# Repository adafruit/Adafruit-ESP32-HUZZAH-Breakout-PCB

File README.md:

## Adafruit HUZZAH32 PCB

<a href="http://www.adafruit.com/products/4172"><br/>
Click here to purchase one from the Adafruit shop</a>

PCB files for the Adafruit HUZZAH32. 

Format is EagleCAD schematic and board layout
* https://www.adafruit.com/product/4172

### Description

Squeeeeze down your next ESP32 project to its bare-bones essential with the **Adafruit HUZZAH32 Breakout**. This breakout is basically the 'big sister' of our HUZZAH 8266, but instead of an ESP8266 it has the '32! We've pared down our popular [Feather ESP32](https://www.adafruit.com/product/3405), removing the battery charger and USB-serial converter. You just get a regulator, some protection diodes, two buttons and an LED. For some projects, where price and size are at a premium, you can program this board over the 'FTDI cable' breakout when needed, and leave it alone otherwise.

Note that this board doesn't come with a USB to serial converter chip and auto-reset circuit. Instead, you will need to plug in a [CP2104 Friend](https://www.adafruit.com/product/3309) or [FTDI cable](https://www.adafruit.com/product/70). Then, before uploading code, put it into bootloader mode by holding down the GPIO #0 button and clicking Reset button, then releasing the #0 button.

That module in the middle of the breakout contains a dual-core ESP32 chip, 4 MB of SPI Flash, tuned antenna, and all the passives you need to take advantage of this powerful new processor. The ESP32 has both WiFi and Bluetooth Classic/LE support. That means it's perfect for just about any wireless or Internet-connected project.

The ESP32 is a perfect upgrade from the ESP8266 that has been so popular. In comparison, the ESP32 has way more GPIO, plenty of analog inputs, two analog outputs, multiple extra peripherals (like a spare UART), two cores so you don't have to yield to the WiFi manager, much higher-speed processor, etc. etc!

Comes fully assembled and tested, pre-programmed with ESP32 SPI WiFi co-processor firmware that [you can use in CircuitPython to use this into a WiFi co-processsor over SPI + 2 pins.](https://github.com/ladyada/Adafruit_CircuitPython_ESP32SPI) We also toss in some header so you can solder it in and plug into a solderless breadboard. 

Here are [specifications from Espressif about the ESP32](https://espressif.com/en/products/hardware/esp32/overview):

 * 240 MHz dual core Tensilica LX6 microcontroller with 600 DMIPS
 * Integrated 520 KB SRAM
 * Integrated 802.11b/g/n HT40 Wi-Fi transceiver, baseband, stack and LWIP
 * Integrated dual mode Bluetooth (classic and BLE)
 * 4 MByte flash include in the WROOM32 module
 * On-board PCB antenna
 * Ultra-low noise analog amplifier
 * Hall sensor
 * 10x capacitive touch interface
 * 32 kHz crystal oscillator
 * 3 x UARTs (only two are configured by default in the Feather Arduino IDE support, one UART is used for bootloading/debug)
 * 3 x SPI (only one is configured by default in the Feather Arduino IDE support)
 * 2 x I2C (only one is configured by default in the Feather Arduino IDE support)
 * 12 x ADC input channels
 * 2 x I2S Audio
 * 2 x DAC
 * PWM/timer input/output available on every GPIO pin
 * OpenOCD debug interface with 32 kB TRAX buffer
 * SDIO master/slave 50 MHz
 * SD-card interface support

### License

Adafruit invests time and resources providing this open source design, please support Adafruit and open-source hardware by purchasing products from [Adafruit](https://www.adafruit.com)!

Designed by Limor Fried/Ladyada for Adafruit Industries.

Creative Commons Attribution/Share-Alike, all text above must be included in any redistribution. 
See license.txt for additional details.

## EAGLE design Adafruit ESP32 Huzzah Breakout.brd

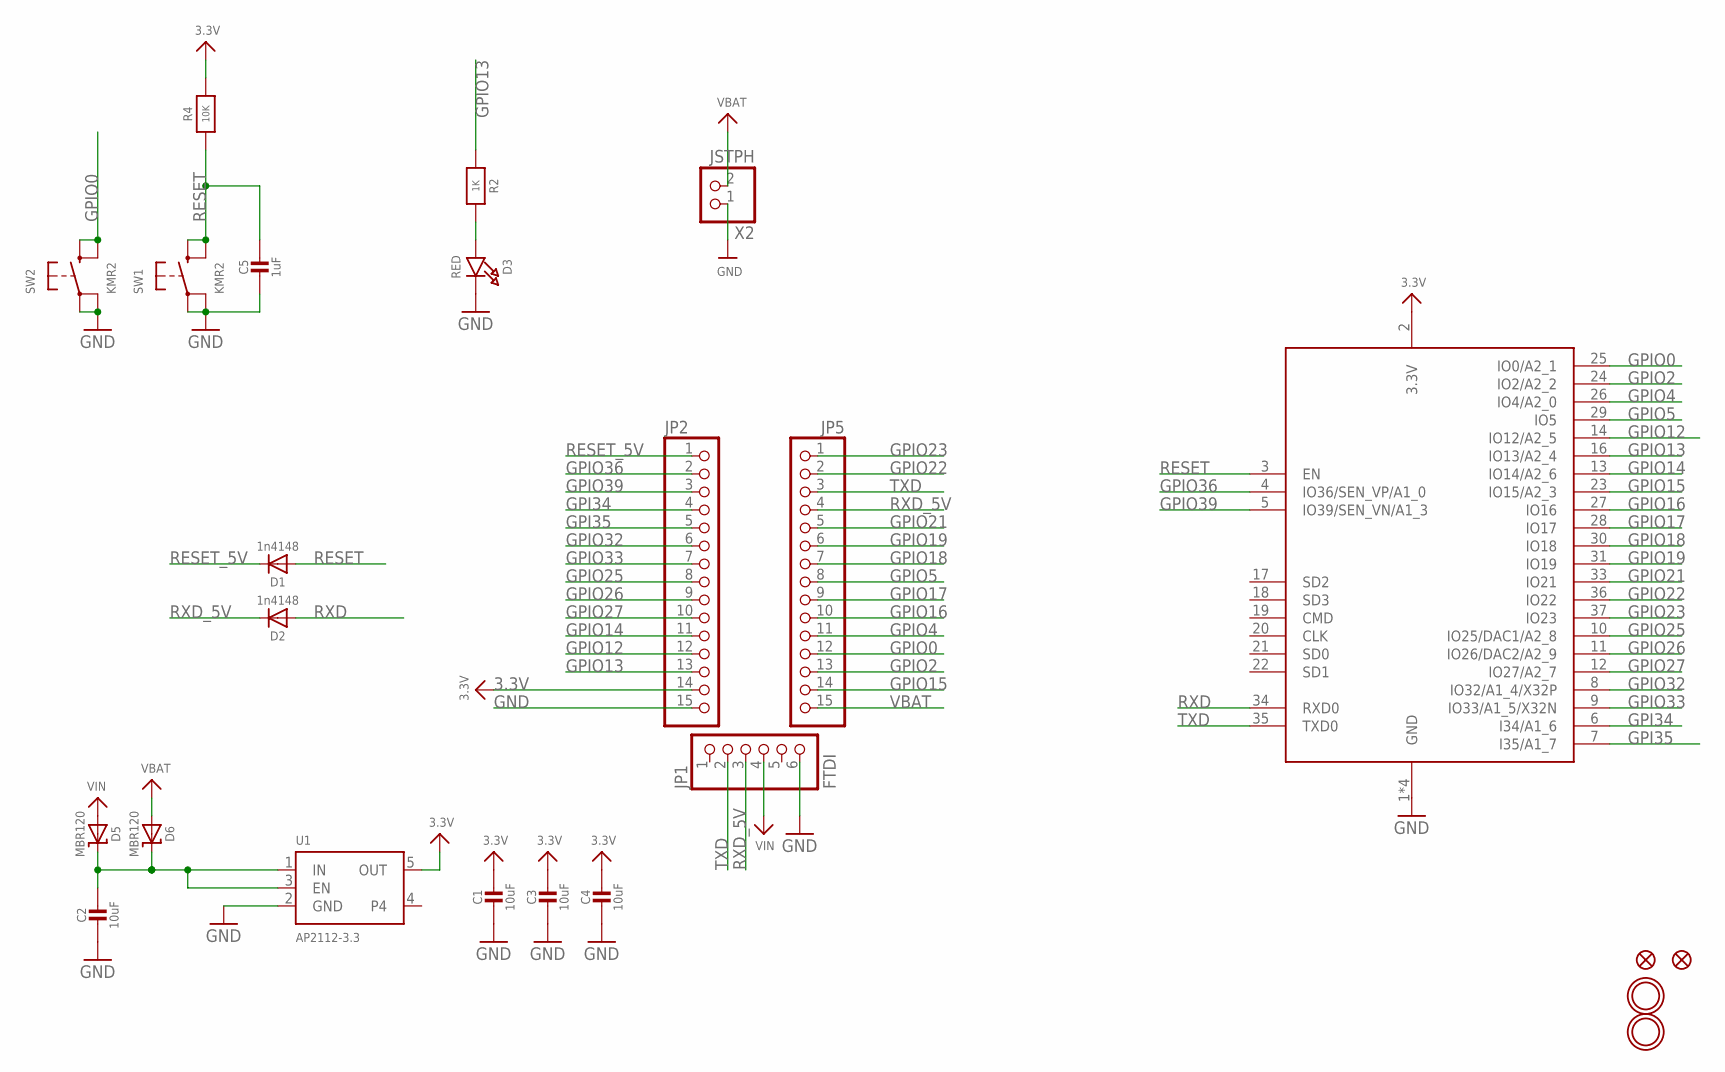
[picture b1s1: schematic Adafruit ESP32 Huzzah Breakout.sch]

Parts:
C1, C2, C3, C4: 10uF; 0805-NO
C5: 1uF; 0805-NO
D1, D2: 1n4148; SOD-323
D3: RED; CHIPLED_0805_NOOUTLINE
D5, D6: MBR120; SOD-123
FID1, FID3: FIDUCIAL_1MM
JP1: FTDI; 1X06_ROUND_70
JP2, JP5: HEADER-1X15; 1X15_ROUND_70
R2: 1K; 0603-NO
R4: 10K; 0603-NO
SW1, SW2: KMR2; BTN_KMR2_4.6X2.8
U1: AP2112-3.3; SOT23-5
U$15, U$16: MOUNTINGHOLE2.5; MOUNTINGHOLE_2.5_PLATED
X1: ESP32_WROOM32; WROOM32
X2: JSTPH; JSTPH2

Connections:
3.3V: C1.1, C3.1, C4.1, JP2.14, R4.2, U1.5 (OUT), X1.2 (3.3V)
GND: C1.2, C2.2, C3.2, C4.2, C5.2, D3.C, JP1.6, JP2.15, SW1.A, SW1.A' (P1), SW2.A, SW2.A' (P1), U1.2 (GND), X1.1 (GND), X1.15 (GND), X1.38 (GND), X1.P$1 (GND), X2.1
GPI34: JP2.4, X1.6 (I34/A1_6)
GPI35: JP2.5, X1.7 (I35/A1_7)
GPIO0: JP5.12, SW2.B (S), SW2.B' (S1), X1.25 (IO0/A2_1)
GPIO2: JP5.13, X1.24 (IO2/A2_2)
GPIO4: JP5.11, X1.26 (IO4/A2_0)
GPIO5: JP5.8, X1.29 (IO5)
GPIO12: JP2.12, X1.14 (IO12/A2_5)
GPIO13: JP2.13, R2.1, X1.16 (IO13/A2_4)
GPIO14: JP2.11, X1.13 (IO14/A2_6)
GPIO15: JP5.14, X1.23 (IO15/A2_3)
GPIO16: JP5.10, X1.27 (IO16)
GPIO17: JP5.9, X1.28 (IO17)
GPIO18: JP5.7, X1.30 (IO18)
GPIO19: JP5.6, X1.31 (IO19)
GPIO21: JP5.5, X1.33 (IO21)
GPIO22: JP5.2, X1.36 (IO22)
GPIO23: JP5.1, X1.37 (IO23)
GPIO25: JP2.8, X1.10 (IO25/DAC1/A2_8)
GPIO26: JP2.9, X1.11 (IO26/DAC2/A2_9)
GPIO27: JP2.10, X1.12 (IO27/A2_7)
GPIO32: JP2.6, X1.8 (IO32/A1_4/X32P)
GPIO33: JP2.7, X1.9 (IO33/A1_5/X32N)
GPIO36: JP2.2, X1.4 (IO36/SEN_VP/A1_0)
GPIO39: JP2.3, X1.5 (IO39/SEN_VN/A1_3)
LDO_EN: C2.1, D5.C, D6.C, U1.1 (IN), U1.3 (EN)
unnamed: D3.A, R2.2
RESET: C5.1, D1.A, R4.1, SW1.B (S), SW1.B' (S1), X1.3 (EN)
RESET_5V: D1.C, JP2.1
RXD: D2.A, X1.34 (RXD0)
RXD_5V: D2.C, JP1.3, JP5.4
TXD: JP1.2, JP5.3, X1.35 (TXD0)
VBAT: D6.A, JP5.15, X2.2
VIN: D5.A, JP1.4

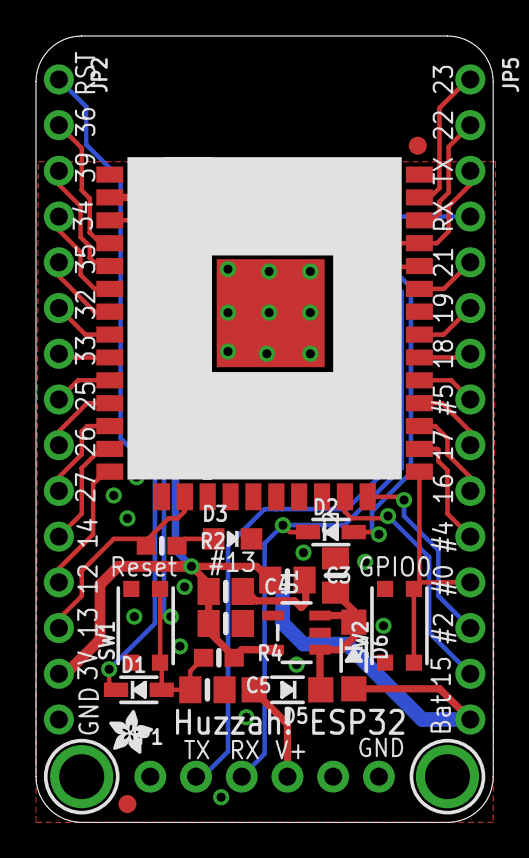
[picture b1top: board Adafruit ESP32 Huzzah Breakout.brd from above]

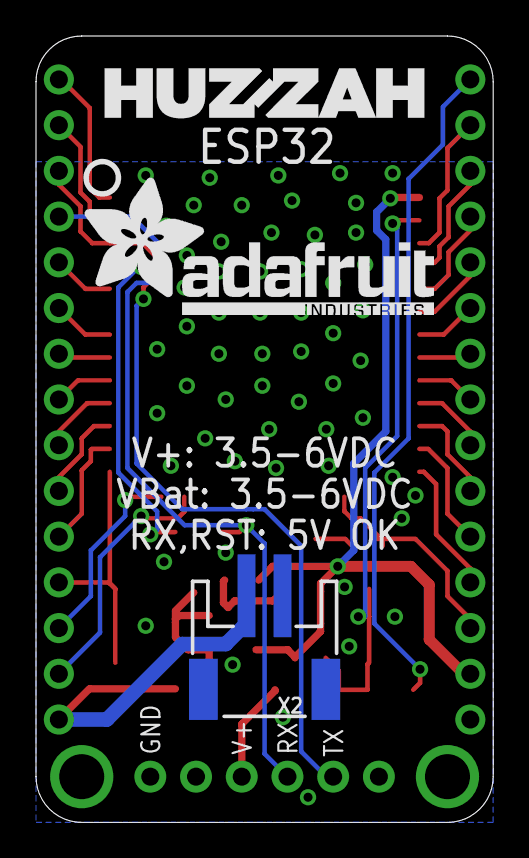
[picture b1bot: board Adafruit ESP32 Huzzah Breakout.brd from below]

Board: 2 copper layers, 25.4 x 43.7 mm, 28 parts (4 on the bottom side), 35 nets.

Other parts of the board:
U$2: HUZZAHLOGO
U$3: ADAFRUIT_2.5MM
U$12: ADAFRUIT_TEXT_20MM
U$13: PCBFEAT-REV-040

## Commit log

2019-04-11 Adding PCB files
2019-07-17 updated to use cookiecutter for pcb repos
2022-06-06 Added Prettypins

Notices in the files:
parts and their libraries:
microbuilder: This work is placed in the public domain, and may be freely used for commercial and non-commercial work with the following conditions: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
